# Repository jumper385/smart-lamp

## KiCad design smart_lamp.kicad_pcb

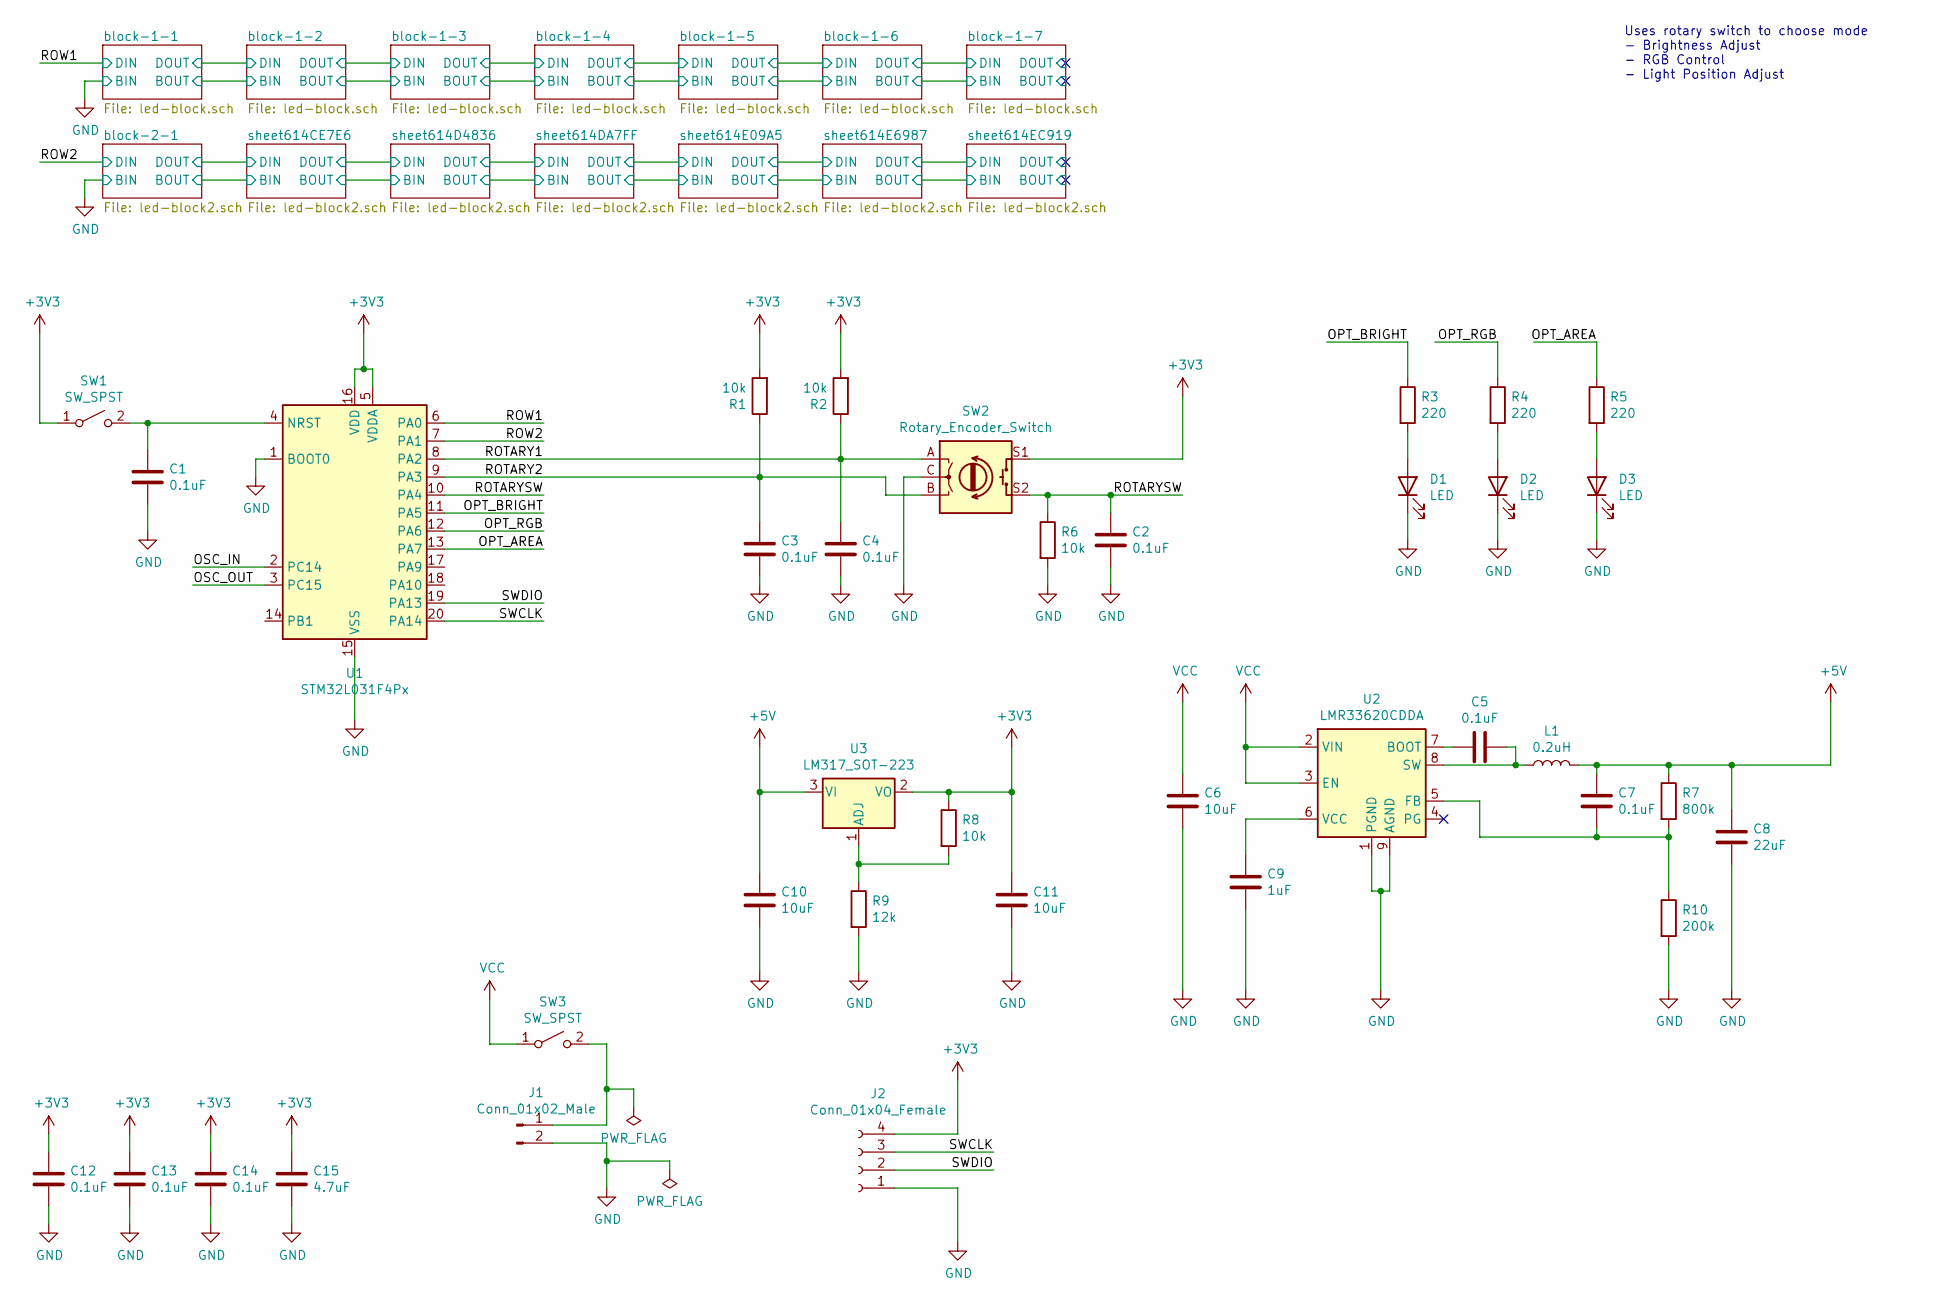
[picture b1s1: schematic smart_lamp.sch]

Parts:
C1, C2, C3, C4, C5, C7, C12, C13, C14: 0.1uF; C_0603_1608Metric
C6, C10, C11: 10uF; C_0603_1608Metric
C8: 22uF; C_0603_1608Metric
C9: 1uF; C_0603_1608Metric
C15: 4.7uF; C_0603_1608Metric
D1, D2, D3: LED; LED_0603_1608Metric
J1: Conn_01x02_Male; BarrelJack_CUI_PJ-063AH_Horizontal
J2: Conn_01x04_Female; PinHeader_1x04_P2.54mm_Vertical
L1: 0.2uH; L_6.3x6.3_H3
R1, R2, R6, R8: 10k; R_0603_1608Metric
R3, R4, R5: 220; R_0603_1608Metric
R7: 800k; R_0603_1608Metric
R9: 12k; R_0603_1608Metric
R10: 200k; R_0603_1608Metric
SW1: SW_SPST; SW_SPST_TL3342
SW2: Rotary_Encoder_Switch; RotaryEncoder_Alps_EC11E-Switch_Vertical_H20mm_CircularMoun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
SW3: SW_SPST; SW_SPDT_PCM12
U1: STM32L031F4Px; TSSOP-20_4.4x6.5mm_P0.65mm
U2: LMR33620CDDA; Texas_HSOP-8-1EP_3.9x4.9mm_P1.27mm_ThermalVias
U3: LM317_SOT-223; SOT-223-3_TabPin2

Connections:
+3V3: C11.1, C12.1, C13.1, C14.1, C15.1, J2.4, R1.2, R2.2, R8.1, SW1.1 (A), SW2.S1, U1.5 (VDDA), U1.16 (VDD), U3.2 (VO)
+5V: C7.1, C8.1, C10.1, L1.2, R7.1, U3.3 (VI); also elsewhere on the board
/OPT_AREA: R5.1, U1.13 (PA7)
/OPT_BRIGHT: R3.1, U1.11 (PA5)
/OPT_RGB: R4.1, U1.12 (PA6)
/ROTARY1: C4.1, R2.1, SW2.A, U1.8 (PA2)
/ROTARY2: C3.1, R1.1, SW2.B, U1.9 (PA3)
/ROTARYSW: C2.1, R6.1, SW2.S2, U1.10 (PA4)
/ROW1: U1.6 (PA0); also elsewhere on the board
/ROW2: U1.7 (PA1); also elsewhere on the board
/SWCLK: J2.3, U1.20 (PA14)
/SWDIO: J2.2, U1.19 (PA13)
GND: C1.2, C2.2, C3.2, C4.2, C6.2, C8.2, C9.2, C10.2, C11.2, C12.2, C13.2, C14.2, C15.2, D1.1 (K), D2.1 (K), D3.1 (K), J1.2, J2.1, R6.2, R9.2, R10.2, SW2.C, U1.1 (BOOT0), U1.15 (VSS), U2.1 (PGND), U2.9 (AGND); also elsewhere on the board
unnamed: C1.1, SW1.2 (B), U1.4 (NRST)
unnamed: C5.1, L1.1, U2.8 (SW)
unnamed: C5.2, U2.7 (BOOT)
unnamed: C7.2, R7.2, R10.1, U2.5 (FB)
unnamed: C9.1, U2.6 (VCC)
unnamed: D1.2 (A), R3.2
unnamed: D2.2 (A), R4.2
unnamed: D3.2 (A), R5.2
unnamed: J1.1, SW3.2 (B)
unnamed: R8.2, R9.1, U3.1 (ADJ)
VCC: C6.1, SW3.1 (A), U2.2 (VIN), U2.3 (EN)

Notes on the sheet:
Uses rotary switch to choose mode - Brightness Adjust - RGB Control - Light Position Adjust

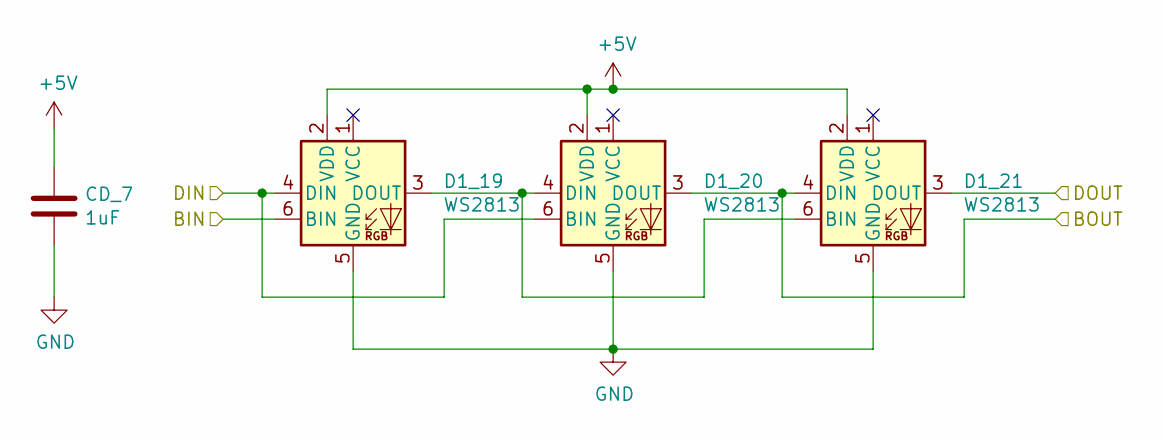
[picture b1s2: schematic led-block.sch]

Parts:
CD_1: 1uF; C_0603_1608Metric
D1_1, D1_2, D1_3: WS2813; LED_WS2812_PLCC6_5.0x5.0mm_P1.6mm

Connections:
+5V: CD_1.1, D1_1.2 (VDD), D1_2.2 (VDD), D1_3.2 (VDD); also elsewhere on the board
/ROW1: D1_1.4 (DIN), D1_2.6 (BIN); also elsewhere on the board
/block-1-2/BIN: D1_2.3 (DOUT), D1_3.4 (DIN); also elsewhere on the board
/block-1-2/DIN: D1_3.3 (DOUT); also elsewhere on the board
GND: CD_1.2, D1_1.5 (GND), D1_1.6 (BIN), D1_2.5 (GND), D1_3.5 (GND); also elsewhere on the board
unnamed: D1_1.3 (DOUT), D1_2.4 (DIN), D1_3.6 (BIN)

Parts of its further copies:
CD_2, CD_3, CD_4, CD_5, CD_6, CD_7: 1uF; C_0603_1608Metric
D1_4, D1_5, D1_6, D1_7, D1_8, D1_9, D1_10, D1_11, D1_12, D1_13, D1_14, D1_15, D1_16, D1_17, D1_18, D1_19, D1_20, D1_21: WS2813; LED_WS2812_PLCC6_5.0x5.0mm_P1.6mm

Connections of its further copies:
+5V: CD_2.1, CD_3.1, CD_4.1, CD_5.1, CD_6.1, CD_7.1, D1_4.2 (VDD), D1_5.2 (VDD), D1_6.2 (VDD), D1_7.2 (VDD), D1_8.2 (VDD), D1_9.2 (VDD), D1_10.2 (VDD), D1_11.2 (VDD), D1_12.2 (VDD), D1_13.2 (VDD), D1_14.2 (VDD), D1_15.2 (VDD), D1_16.2 (VDD), D1_17.2 (VDD), D1_18.2 (VDD), D1_19.2 (VDD), D1_20.2 (VDD), D1_21.2 (VDD); also elsewhere on the board
/block-1-2/BIN: D1_4.6 (BIN); also elsewhere on the board
/block-1-2/DIN: D1_4.4 (DIN), D1_5.6 (BIN); also elsewhere on the board
/block-1-3/BIN: D1_5.3 (DOUT), D1_6.4 (DIN), D1_7.6 (BIN)
/block-1-3/DIN: D1_6.3 (DOUT), D1_7.4 (DIN), D1_8.6 (BIN)
/block-1-4/BIN: D1_8.3 (DOUT), D1_9.4 (DIN), D1_10.6 (BIN)
/block-1-4/DIN: D1_9.3 (DOUT), D1_10.4 (DIN), D1_11.6 (BIN)
/block-1-5/BIN: D1_11.3 (DOUT), D1_12.4 (DIN), D1_13.6 (BIN)
/block-1-5/DIN: D1_12.3 (DOUT), D1_13.4 (DIN), D1_14.6 (BIN)
/block-1-6/BIN: D1_14.3 (DOUT), D1_15.4 (DIN), D1_16.6 (BIN)
/block-1-6/DIN: D1_15.3 (DOUT), D1_16.4 (DIN), D1_17.6 (BIN)
/block-1-7/BIN: D1_17.3 (DOUT), D1_18.4 (DIN), D1_19.6 (BIN)
/block-1-7/BOUT: D1_20.3 (DOUT), D1_21.4 (DIN)
/block-1-7/DIN: D1_18.3 (DOUT), D1_19.4 (DIN), D1_20.6 (BIN)
GND: CD_2.2, CD_3.2, CD_4.2, CD_5.2, CD_6.2, CD_7.2, D1_4.5 (GND), D1_5.5 (GND), D1_6.5 (GND), D1_7.5 (GND), D1_8.5 (GND), D1_9.5 (GND), D1_10.5 (GND), D1_11.5 (GND), D1_12.5 (GND), D1_13.5 (GND), D1_14.5 (GND), D1_15.5 (GND), D1_16.5 (GND), D1_17.5 (GND), D1_18.5 (GND), D1_19.5 (GND), D1_20.5 (GND), D1_21.5 (GND); also elsewhere on the board
unnamed: D1_4.3 (DOUT), D1_5.4 (DIN), D1_6.6 (BIN)
unnamed: D1_7.3 (DOUT), D1_8.4 (DIN), D1_9.6 (BIN)
unnamed: D1_10.3 (DOUT), D1_11.4 (DIN), D1_12.6 (BIN)
unnamed: D1_13.3 (DOUT), D1_14.4 (DIN), D1_15.6 (BIN)
unnamed: D1_16.3 (DOUT), D1_17.4 (DIN), D1_18.6 (BIN)
unnamed: D1_19.3 (DOUT), D1_20.4 (DIN), D1_21.6 (BIN)

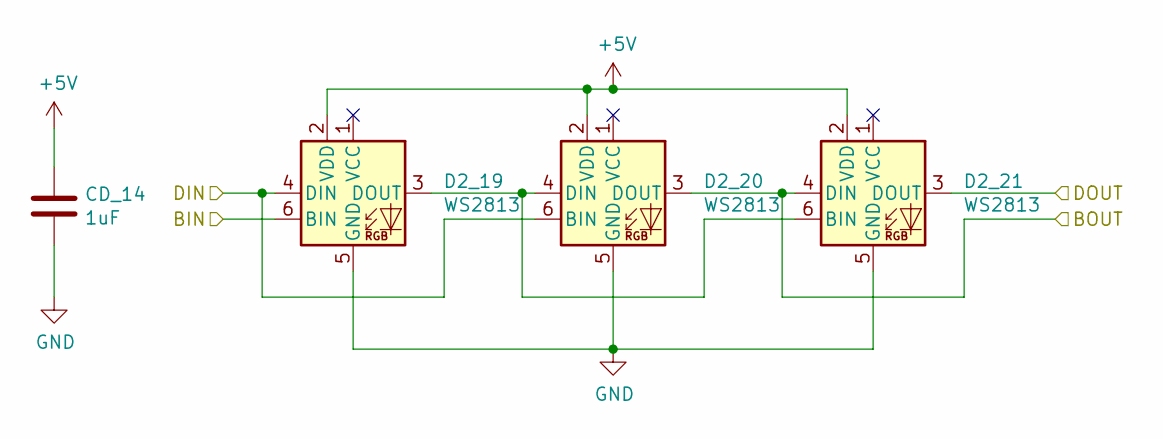
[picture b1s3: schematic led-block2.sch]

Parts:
CD_11: 1uF; C_0603_1608Metric
D2_1, D2_2, D2_3: WS2813; LED_WS2812_PLCC6_5.0x5.0mm_P1.6mm

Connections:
+5V: CD_11.1, D2_1.2 (VDD), D2_2.2 (VDD), D2_3.2 (VDD); also elsewhere on the board
/ROW2: D2_1.4 (DIN), D2_2.6 (BIN); also elsewhere on the board
/sheet614CE7E6/BIN: D2_2.3 (DOUT), D2_3.4 (DIN); also elsewhere on the board
/sheet614CE7E6/DIN: D2_3.3 (DOUT); also elsewhere on the board
GND: CD_11.2, D2_1.5 (GND), D2_1.6 (BIN), D2_2.5 (GND), D2_3.5 (GND); also elsewhere on the board
unnamed: D2_1.3 (DOUT), D2_2.4 (DIN), D2_3.6 (BIN)

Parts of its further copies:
CD_8, CD_9, CD_10, CD_12, CD_13, CD_14: 1uF; C_0603_1608Metric
D2_4, D2_5, D2_6, D2_7, D2_8, D2_9, D2_10, D2_11, D2_12, D2_13, D2_14, D2_15, D2_16, D2_17, D2_18, D2_19, D2_20, D2_21: WS2813; LED_WS2812_PLCC6_5.0x5.0mm_P1.6mm

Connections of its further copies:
+5V: CD_8.1, CD_9.1, CD_10.1, CD_12.1, CD_13.1, CD_14.1, D2_4.2 (VDD), D2_5.2 (VDD), D2_6.2 (VDD), D2_7.2 (VDD), D2_8.2 (VDD), D2_9.2 (VDD), D2_10.2 (VDD), D2_11.2 (VDD), D2_12.2 (VDD), D2_13.2 (VDD), D2_14.2 (VDD), D2_15.2 (VDD), D2_16.2 (VDD), D2_17.2 (VDD), D2_18.2 (VDD), D2_19.2 (VDD), D2_20.2 (VDD), D2_21.2 (VDD); also elsewhere on the board
/sheet614CE7E6/BIN: D2_4.6 (BIN); also elsewhere on the board
/sheet614CE7E6/DIN: D2_4.4 (DIN), D2_5.6 (BIN); also elsewhere on the board
/sheet614D4836/BIN: D2_5.3 (DOUT), D2_6.4 (DIN), D2_7.6 (BIN)
/sheet614D4836/DIN: D2_6.3 (DOUT), D2_7.4 (DIN), D2_8.6 (BIN)
/sheet614DA7FF/BIN: D2_8.3 (DOUT), D2_9.4 (DIN), D2_10.6 (BIN)
/sheet614DA7FF/DIN: D2_9.3 (DOUT), D2_10.4 (DIN), D2_11.6 (BIN)
/sheet614E09A5/BIN: D2_11.3 (DOUT), D2_12.4 (DIN), D2_13.6 (BIN)
/sheet614E09A5/DIN: D2_12.3 (DOUT), D2_13.4 (DIN), D2_14.6 (BIN)
/sheet614E6987/BIN: D2_14.3 (DOUT), D2_15.4 (DIN), D2_16.6 (BIN)
/sheet614E6987/DIN: D2_15.3 (DOUT), D2_16.4 (DIN), D2_17.6 (BIN)
/sheet614EC919/BIN: D2_17.3 (DOUT), D2_18.4 (DIN), D2_19.6 (BIN)
/sheet614EC919/BOUT: D2_20.3 (DOUT), D2_21.4 (DIN)
/sheet614EC919/DIN: D2_18.3 (DOUT), D2_19.4 (DIN), D2_20.6 (BIN)
GND: CD_8.2, CD_9.2, CD_10.2, CD_12.2, CD_13.2, CD_14.2, D2_4.5 (GND), D2_5.5 (GND), D2_6.5 (GND), D2_7.5 (GND), D2_8.5 (GND), D2_9.5 (GND), D2_10.5 (GND), D2_11.5 (GND), D2_12.5 (GND), D2_13.5 (GND), D2_14.5 (GND), D2_15.5 (GND), D2_16.5 (GND), D2_17.5 (GND), D2_18.5 (GND), D2_19.5 (GND), D2_20.5 (GND), D2_21.5 (GND); also elsewhere on the board
unnamed: D2_4.3 (DOUT), D2_5.4 (DIN), D2_6.6 (BIN)
unnamed: D2_7.3 (DOUT), D2_8.4 (DIN), D2_9.6 (BIN)
unnamed: D2_10.3 (DOUT), D2_11.4 (DIN), D2_12.6 (BIN)
unnamed: D2_13.3 (DOUT), D2_14.4 (DIN), D2_15.6 (BIN)
unnamed: D2_16.3 (DOUT), D2_17.4 (DIN), D2_18.6 (BIN)
unnamed: D2_19.3 (DOUT), D2_20.4 (DIN), D2_21.6 (BIN)

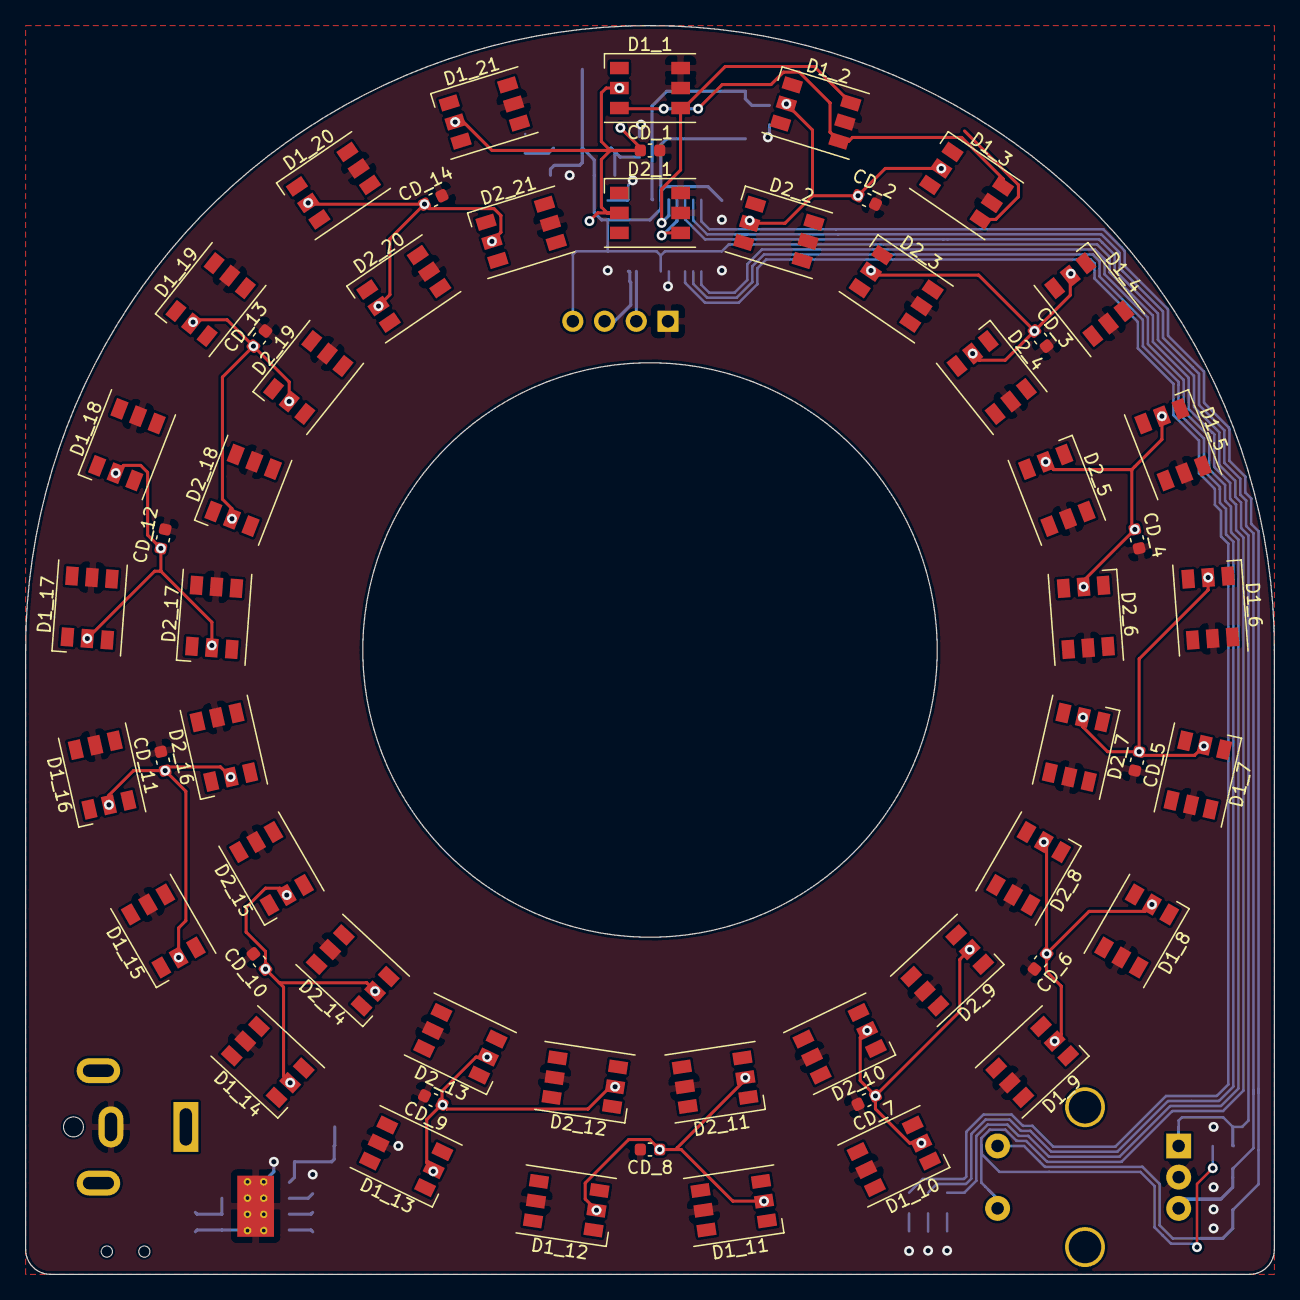
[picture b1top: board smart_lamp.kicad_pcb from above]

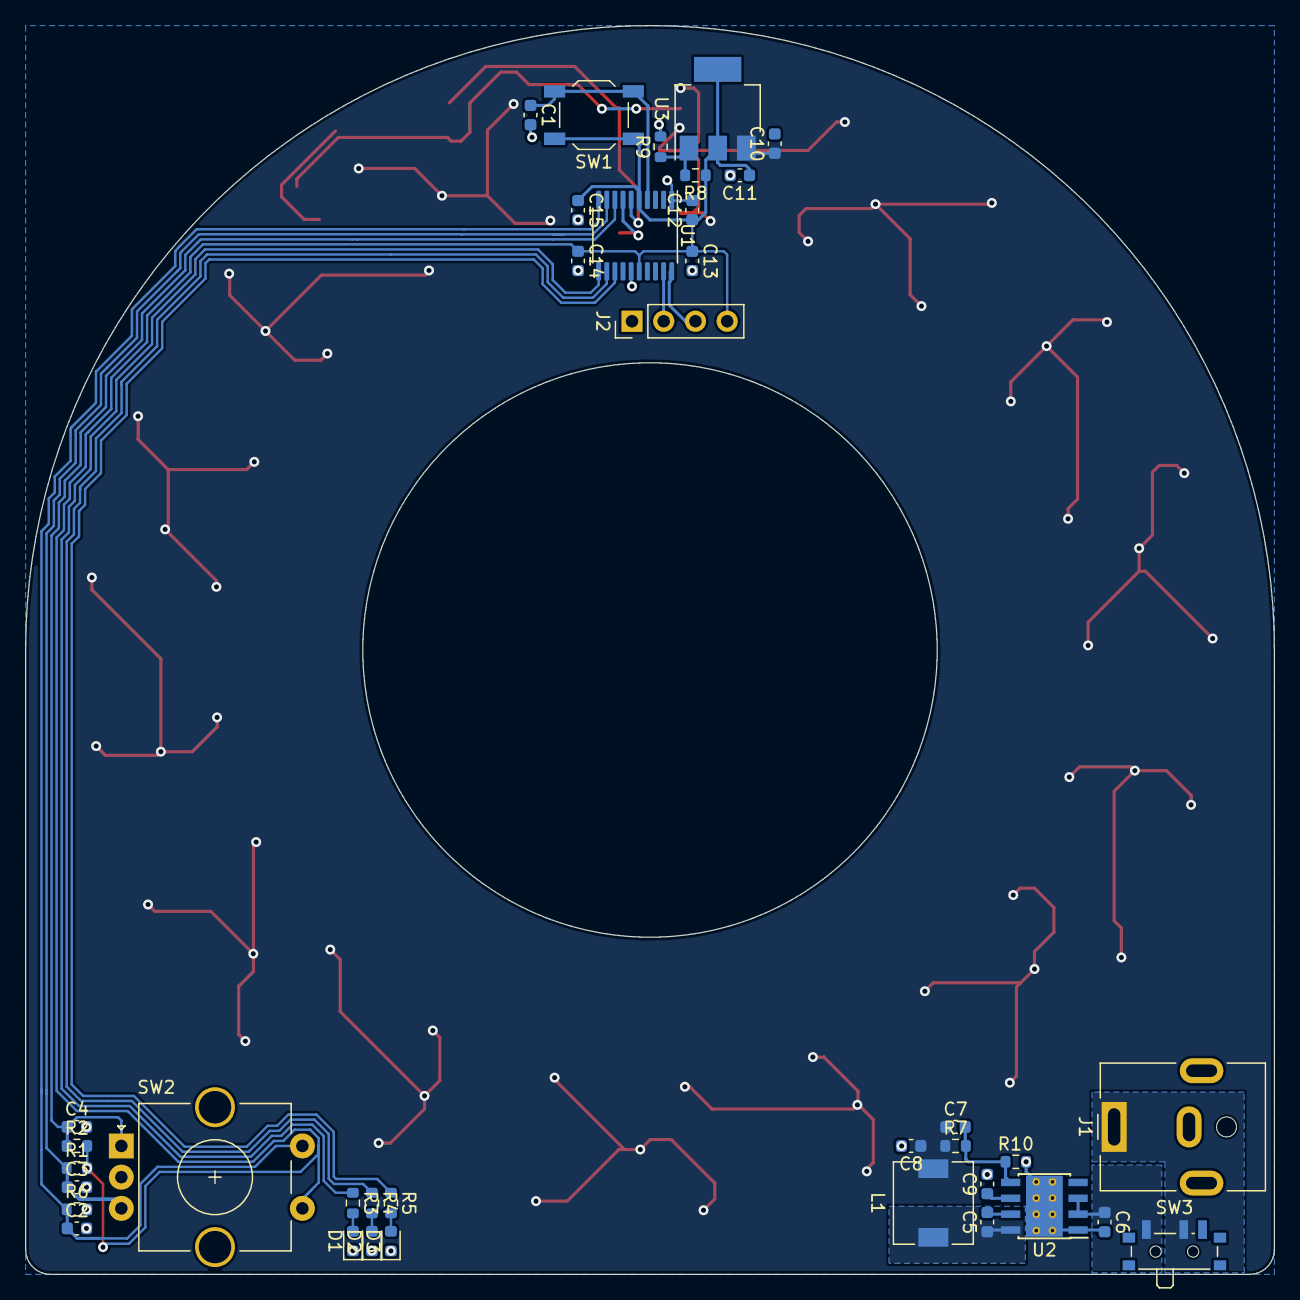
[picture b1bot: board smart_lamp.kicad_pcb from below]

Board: 2 copper layers, 100.0 x 100.0 mm, 93 parts (37 on the bottom side), 64 nets.
